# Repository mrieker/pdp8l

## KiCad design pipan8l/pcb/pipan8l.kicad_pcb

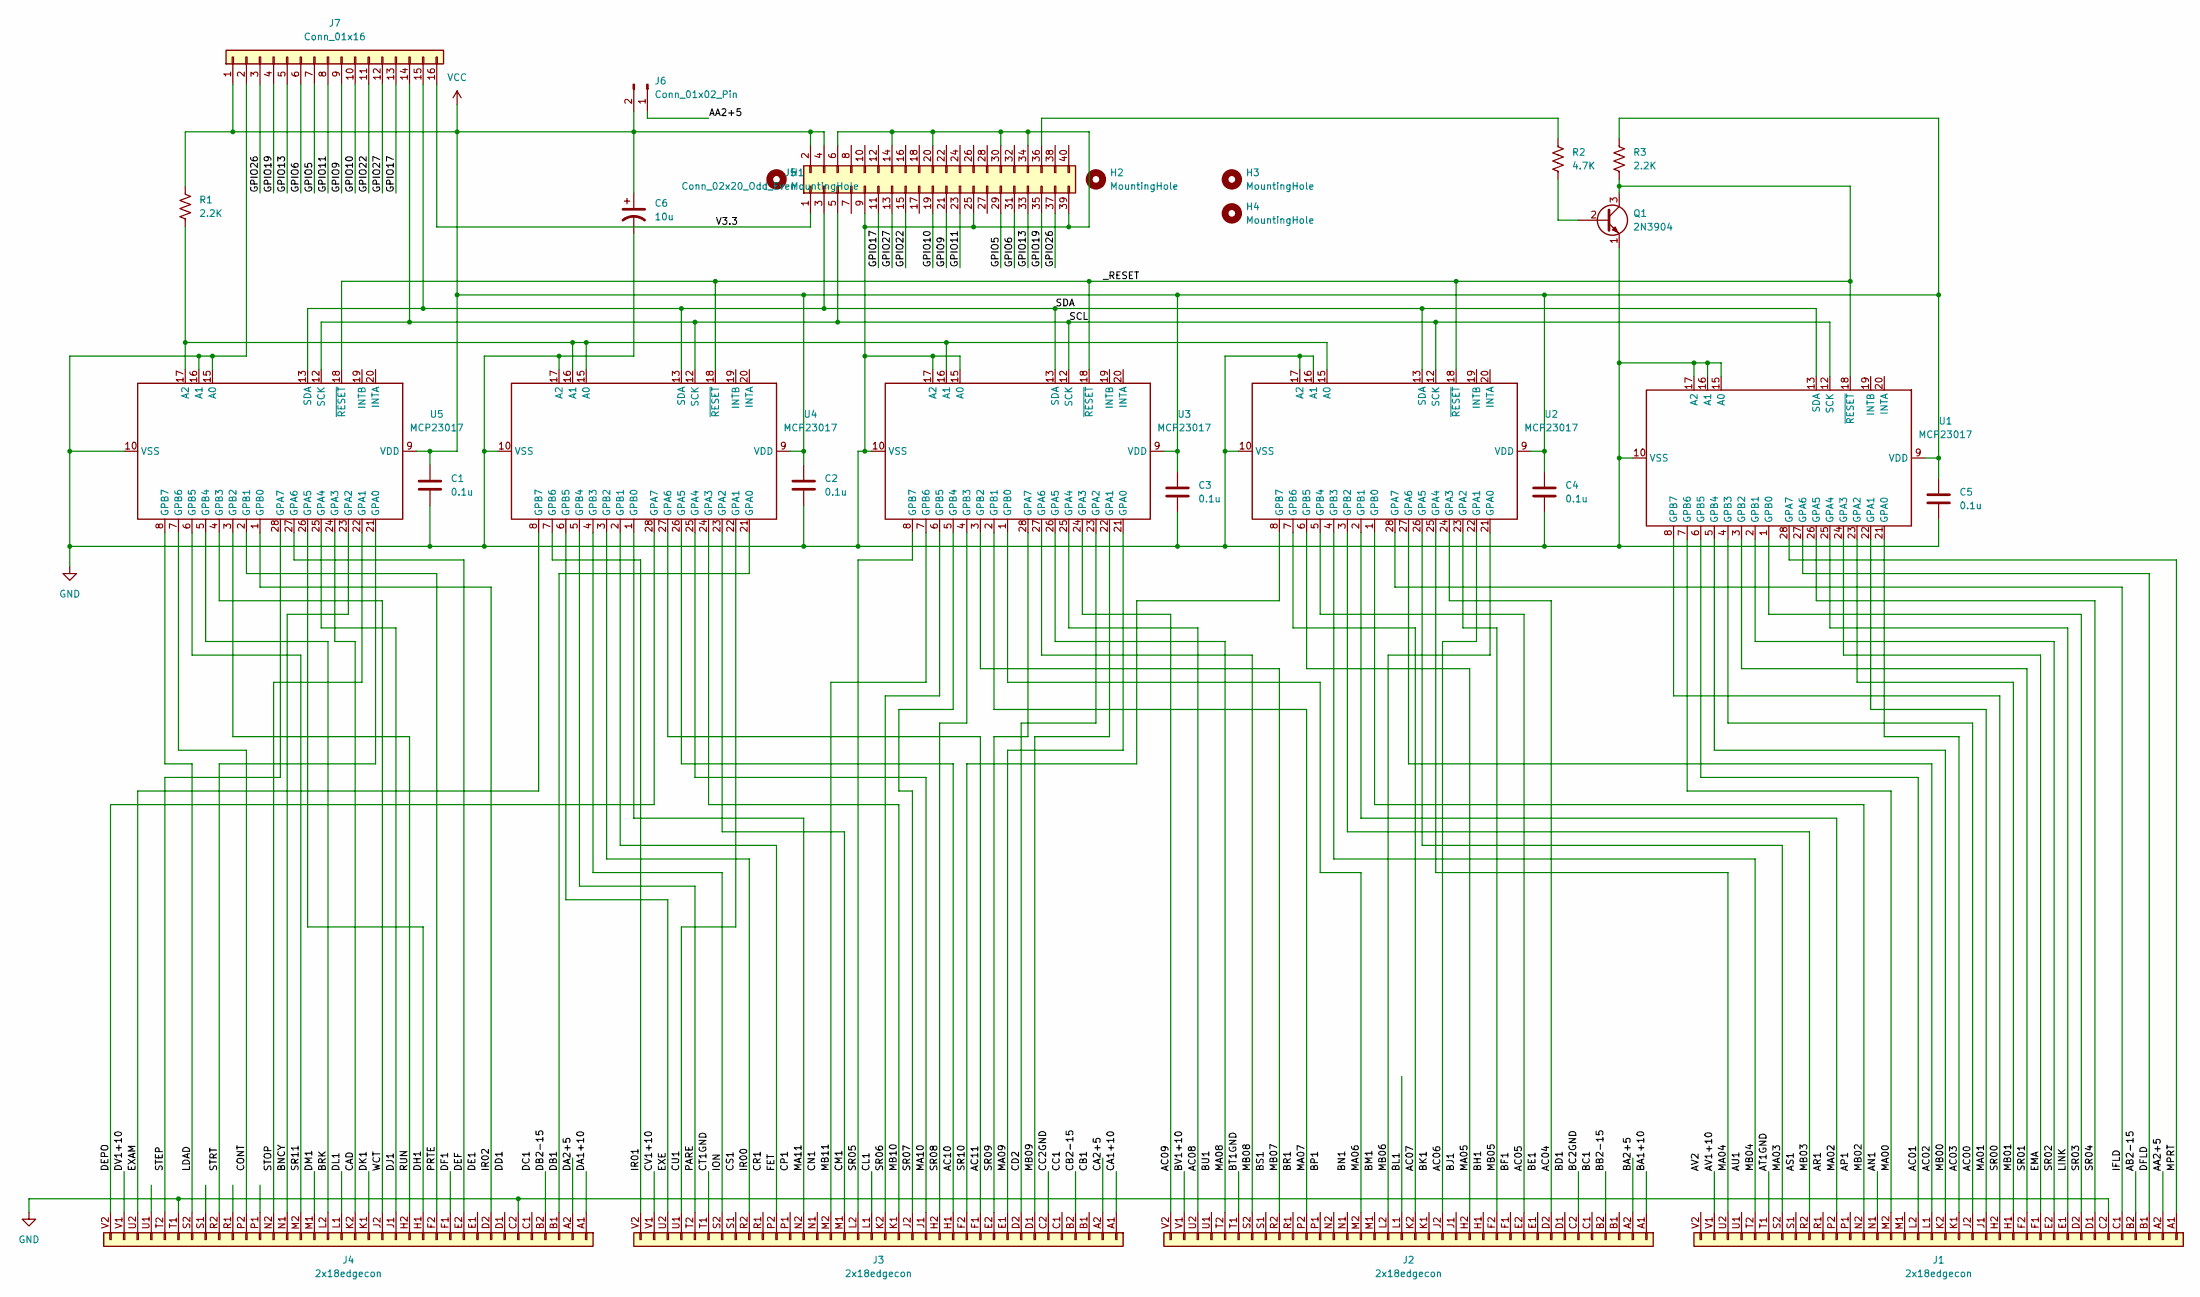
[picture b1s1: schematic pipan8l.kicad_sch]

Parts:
C1, C2, C3, C4, C5: 0.1u; C_Axial_L3.8mm_D2.6mm_P7.50mm_Horizontal
C6: 10u; CP_Axial_L11.0mm_D5.0mm_P18.00mm_Horizontal
H1, H2: MountingHole; MountingHole_3mm
H3, H4: MountingHole; MountingHole_8.4mm_M8
J1, J2, J3, J4: 2x18edgecon; 2x18-edge
J5: Conn_02x20_Odd_Even; PinHeader_2x20_P2.54mm_Vertical
J6: Conn_01x02_Pin; PinHeader_1x02_P2.54mm_Vertical
J7: Conn_01x16; PinHeader_1x16_P2.54mm_Horizontal
Q1: 2N3904; TO-92_Wide
R1, R3: 2.2K; R_Axial_DIN0207_L6.3mm_D2.5mm_P10.16mm_Horizontal
R2: 4.7K; R_Axial_DIN0207_L6.3mm_D2.5mm_P10.16mm_Horizontal
U1, U2, U3, U4, U5: MCP23017; DIP-28_W7.62mm_LongPads

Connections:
/AA2+5: J1.A2, J6.1
/AB2-15: J1.B2
/AC00: J1.J2, U1.4 (GPB3)
/AC01: J1.L2, U1.6 (GPB5)
/AC02: J1.L1, U2.27 (GPA6)
/AC03: J1.K1, U1.21 (GPA0)
/AC04: J2.D2, U2.24 (GPA3)
/AC05: J2.E2, U2.5 (GPB4)
/AC06: J2.J2, U2.22 (GPA1)
/AC07: J2.K2, U2.7 (GPB6)
/AC08: J2.U2, U3.25 (GPA4)
/AC09: J2.V2, U3.24 (GPA3)
/AC10: J3.H1, U4.26 (GPA5)
/AC11: J3.F1, U4.27 (GPA6)
/AN1: J1.N1
/AT1GND: J1.T1
/AV1+10: J1.V1
/BA1+10: J2.A1
/BA2+5: J2.A2
/BB2-15: J2.B2
/BC2GND: J2.C2
/BL1: J2.L1
/BNCY: J4.N1, U5.23 (GPA2)
/BRK: J4.L2, U5.5 (GPB4)
/BT1GND: J2.T1
/BV1+10: J2.V1
/CA1+10: J3.A1
/CA2+5: J3.A2
/CAD: J4.K2, U5.24 (GPA3)
/CB2-15: J3.B2
/CC2GND: J3.C2
/CD2: J3.D2, U3.23 (GPA2)
/CL1: J3.L1
/CM1: J3.M1, U4.23 (GPA2)
/CONT: J4.P2, U5.7 (GPB6)
/CT1GND: J3.T1
/CU1: J3.U1, U4.22 (GPA1)
/CV1+10: J3.V1
/DA1+10: J4.A1
/DA2+5: J4.A2
/DB1: J4.B1, U4.21 (GPA0)
/DB2-15: J4.B2
/DEF: J4.E2, U5.27 (GPA6)
/DEPO: J4.V2, U4.28 (GPA7)
/DF1: J4.F1
/DFLD: J1.B1, U1.27 (GPA6)
/DH1: J4.H1, U5.26 (GPA5)
/DJ1: J4.J1, U5.25 (GPA4)
/DK1: J4.K1
/DL1: J4.L1
/DM1: J4.M1
/DV1+10: J4.V1
/EMA: J1.F1, U1.24 (GPA3)
/EXAM: J4.U2, U4.8 (GPB7)
/EXE: J3.U2, U4.6 (GPB5)
/FET: J3.P2, U4.2 (GPB1)
/GPIO5: J5.29, J7.7
/GPIO6: J5.31, J7.6
/GPIO9: J5.21, J7.9
/GPIO10: J5.19, J7.10
/GPIO11: J5.23, J7.8
/GPIO13: J5.33, J7.5
/GPIO17: J5.11, J7.13
/GPIO19: J5.35, J7.4
/GPIO22: J5.15, J7.11
/GPIO26: J5.37, J7.3
/GPIO27: J5.13, J7.12
/IFLD: J1.C1, U2.28 (GPA7)
/ION: J3.S2, U4.4 (GPB3)
/IR00: J3.R2, U4.3 (GPB2)
/IR01: J3.V2, U4.7 (GPB6)
/IR02: J4.D2, U5.1 (GPB0)
/LDAD: J4.S2, U5.8 (GPB7)
/LINK: J1.E1, U1.25 (GPA4)
/MA00: J1.M2, U1.7 (GPB6)
/MA01: J1.J1, U1.22 (GPA1)
/MA02: J1.P2, U2.2 (GPB1)
/MA03: J1.S2, U2.26 (GPA5)
/MA04: J1.U2, U2.25 (GPA4)
/MA05: J2.H2, U2.6 (GPB5)
/MA06: J2.M2, U3.1 (GPB0)
/MA07: J2.P2, U3.2 (GPB1)
/MA08: J2.T2, U3.26 (GPA5)
/MA09: J3.E1, U3.21 (GPA0)
/MA10: J3.J1, U4.25 (GPA4)
/MA11: J3.N2, U4.1 (GPB0)
/MB00: J1.K2, U1.5 (GPB4)
/MB01: J1.H1, U1.23 (GPA2)
/MB02: J1.N2, U2.1 (GPB0)
/MB03: J1.R2, U2.3 (GPB2)
/MB04: J1.T2, U2.4 (GPB3)
/MB05: J2.F2, U2.23 (GPA2)
/MB06: J2.L2, U2.21 (GPA0)
/MB07: J2.R2, U3.3 (GPB2)
/MB08: J2.S2, U3.27 (GPA6)
/MB09: J3.D1, U3.22 (GPA1)
/MB10: J3.K1, U4.24 (GPA3)
/MB11: J3.M2, U3.7 (GPB6)
/MPRT: J1.A1, U1.28 (GPA7)
/PARE: J3.T2, U4.5 (GPB4)
/PRTE: J4.F2, U5.2 (GPB1)
/RUN: J4.H2, U5.3 (GPB2)
/SCL: J5.5, J7.14, U1.12 (SCK), U2.12 (SCK), U3.12 (SCK), U4.12 (SCK), U5.12 (SCK)
/SDA: J5.3, J7.15, U1.13 (SDA), U2.13 (SDA), U3.13 (SDA), U4.13 (SDA), U5.13 (SDA)
/SR00: J1.H2, U1.8 (GPB7)
/SR01: J1.F2, U1.3 (GPB2)
/SR02: J1.E2, U1.2 (GPB1)
/SR03: J1.D2, U1.1 (GPB0)
/SR04: J1.D1, U1.26 (GPA5)
/SR05: J3.L2, U3.8 (GPB7)
/SR06: J3.K2, U3.6 (GPB5)
/SR07: J3.J2, U3.5 (GPB4)
/SR08: J3.H2, U3.4 (GPB3)
/SR09: J3.E2, U3.28 (GPA7)
/SR10: J3.F2, U2.8 (GPB7)
/SR11: J4.M2, U5.6 (GPB5)
/STEP: J4.T2, U5.28 (GPA7)
/STOP: J4.N2, U5.22 (GPA1)
/STRT: J4.R2, U5.21 (GPA0)
/V3.3: J5.1, J7.16
/WCT: J4.J2, U5.4 (GPB3)
/_RESET: Q1.3 (C), R3.2, U1.18 (~RESET), U2.18 (~RESET), U3.18 (~RESET), U4.18 (~RESET), U5.18 (~RESET)
GND: C1.2, C2.2, C3.2, C4.2, C5.2, C6.2, J1.C2, J4.C2, J4.T1, J5.6, J5.9, J5.14, J5.20, J5.25, J5.30, J5.34, J5.39, J7.2, Q1.1 (E), U1.10 (VSS), U1.15 (A0), U1.16 (A1), U1.17 (A2), U2.10 (VSS), U2.16 (A1), U2.17 (A2), U3.10 (VSS), U3.15 (A0), U3.17 (A2), U4.10 (VSS), U4.17 (A2), U5.10 (VSS), U5.15 (A0), U5.16 (A1)
unnamed: J5.36, R2.1
unnamed: Q1.2 (B), R2.2
unnamed: R1.2, U2.15 (A0), U3.16 (A1), U4.15 (A0), U4.16 (A1), U5.17 (A2)
VCC: C1.1, C2.1, C3.1, C4.1, C5.1, C6.1, J5.2, J5.4, J6.2, J7.1, R1.1, R3.1, U1.9 (VDD), U2.9 (VDD), U3.9 (VDD), U4.9 (VDD), U5.9 (VDD)

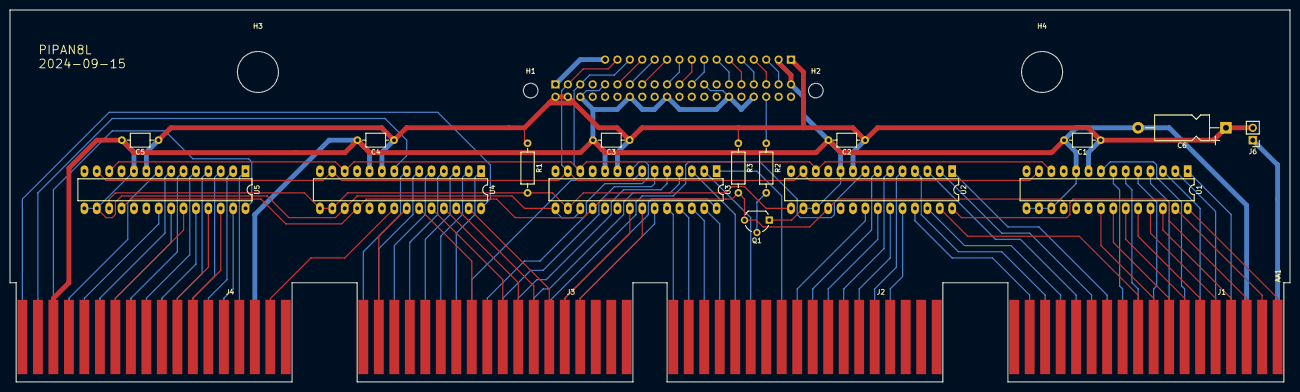
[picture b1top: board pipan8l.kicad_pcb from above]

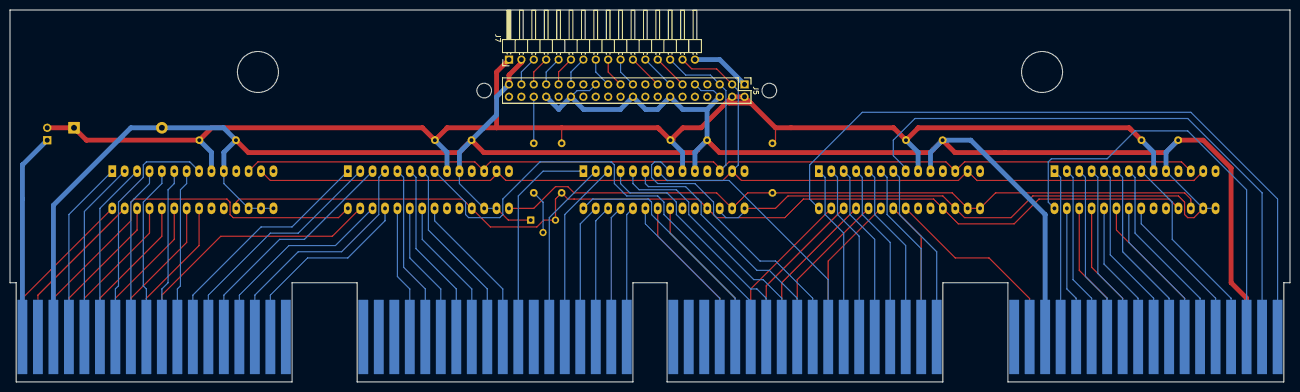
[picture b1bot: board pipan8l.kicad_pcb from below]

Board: 2 copper layers, 262.3 x 76.2 mm, 26 parts (2 on the bottom side), 101 nets.
